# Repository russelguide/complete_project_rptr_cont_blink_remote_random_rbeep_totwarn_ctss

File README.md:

Radio Talking Repeater Controller This is a basic repeater controller. It has a Time speaking clock, blinking led, dfmf remonte control decoder, random rogerbeep function, time out timer for potection and ctcss dedoder, squelch tail timer and Ider timer. The timer lengths can all be changed in the source code. There is an Ider which runs at the end of the Id timer. The Ider message is sent in CW and the message can be change using the Letter codes listed at the end of the source code. There’s an audio control circuit suggestion, which you may find useful. Additionally there should be some type of debounce added to the COS input of the Arduino. Perhaps a cap and resistor to smooth out the CAS transition. This interface will depend on the radio circuit being used.

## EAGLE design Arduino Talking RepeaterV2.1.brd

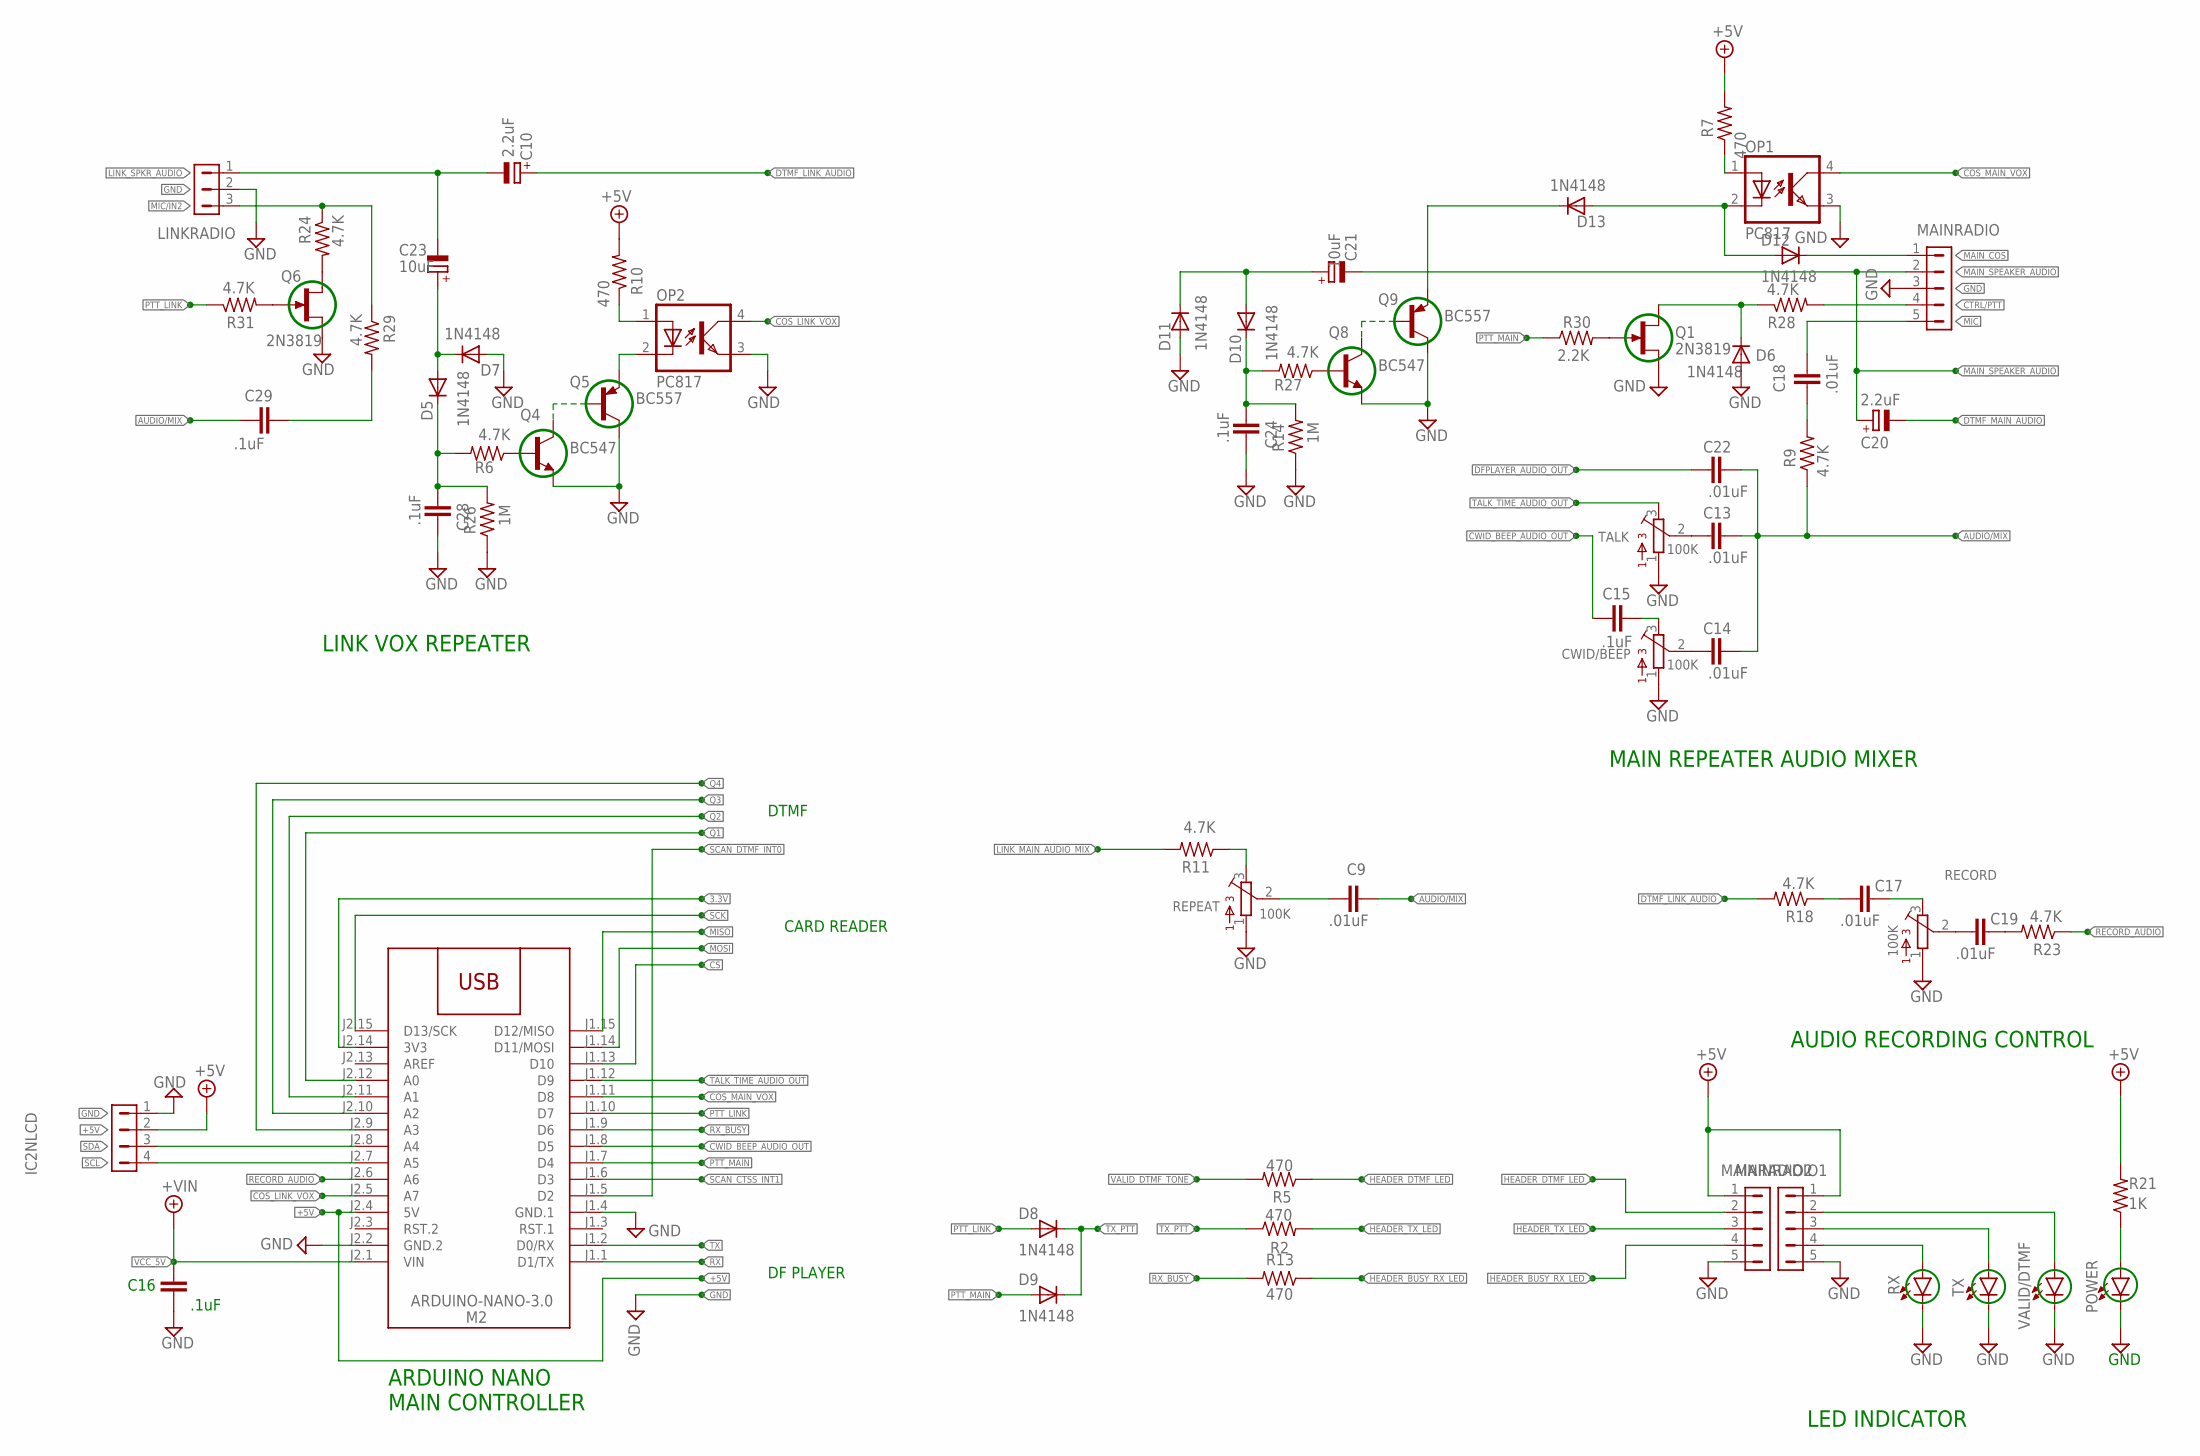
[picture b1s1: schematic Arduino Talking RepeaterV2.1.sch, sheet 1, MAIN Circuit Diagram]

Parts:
C9, C13, C14, C17, C18, C19, C22: .01uF; C5B3
C10, C20: 2.2uF; E2,5-6
C15, C16, C24, C28, C29: .1uF; C5B3
C21, C23: 10uF; E2,5-6
CWID/BEEP: 100K; 3362P
D5, D6, D7, D8, D9, D10, D11, D12, D13: 1N4148; DO35-10
IC2NLCD: HDR-1X4-70543-?; 70543-04
LINKRADIO: HDR-1X3-70543-?; 70543-03
M2: ARDUINO-NANO-3.0
MAINRADIO, MAINRADIO1, MAINRADIO2: HDR-1X5-70543-?; 70543-05
OP1, OP2: PC817; DIL04
POWER: LEDB155; Q62902-B155
Q1, Q6: 2N3819; TO92F
Q4, Q8: BC547; TO92
Q5, Q9: BC557; TO92
R2, R5, R7, R10, R13: 470; 0207/10
R6, R9, R11, R18, R23, R24, R27, R28, R29, R31: 4.7K; 0207/10
R14, R26: 1M; 0207/10
R21: 1K; 0207/10
R30: 2.2K; 0207/10
RECORD: 100K; 3362P
REPEAT: 100K; 3362P
RX: LEDB155; Q62902-B155
TALK: 100K; 3362P
TX: LEDB155; Q62902-B155
VALID/DTMF: LEDB155; Q62902-B155

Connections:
3.3V: M2.J2.14 (3V3); also elsewhere on the board
+5V: IC2NLCD.2, M2.J2.4 (5V), R7.2, R10.2; also elsewhere on the board
AUDIO/MIX: C9.1, C13.1, C14.1, C22.1, C29.1, R9.1
BUSY_RX_LED: MAINRADIO2.4, RX.A (ANODE)
COR: D12.A, D13.A, OP1.2 (C)
COR1: OP2.2 (C), Q5.1 (E)
COS_LINK_VOX: M2.J2.5 (A7), OP2.4 (COL)
COS_MAIN_VOX: M2.J1.11 (D8), OP1.4 (COL)
CS: M2.J1.13 (D10); also elsewhere on the board
CTRL/PTT: MAINRADIO.4, R28.2
CWID_BEEP_AUDIO_OUT: C15.1, M2.J1.8 (D5)
DFPLAYER_AUDIO_OUT: C22.2; also elsewhere on the board
DTMF_LED: MAINRADIO2.2, VALID/DTMF.A (ANODE)
DTMF_LINK_AUDIO: C10.+, R18.2; also elsewhere on the board
DTMF_MAIN_AUDIO: C20.-; also elsewhere on the board
GND: C16.2, C24.1, C28.1, CWID/BEEP.1, D6.A, D7.A, D11.A, IC2NLCD.1, LINKRADIO.2, M2.J1.4 (GND.1), M2.J2.2 (GND.2), MAINRADIO.3, MAINRADIO1.5, MAINRADIO2.5, OP1.3 (EMIT), OP2.3 (EMIT), POWER.K (CATHODE), Q1.S, Q4.1 (E), Q5.3 (C), Q6.S, Q8.1 (E), Q9.3 (C), R14.1, R26.1, RECORD.1, REPEAT.1, RX.K (CATHODE), TALK.1, TX.K (CATHODE), VALID/DTMF.K (CATHODE); also elsewhere on the board
HEADER_BUSY_RX_LED: MAINRADIO1.4, R13.1
HEADER_DTMF_LED: MAINRADIO1.2, R5.1
HEADER_TX_LED: MAINRADIO1.3, R2.2
LINK_MAIN_AUDIO_MIX: R11.2; also elsewhere on the board
LINK_SPKR_AUDIO: C10.-, C23.-, LINKRADIO.1
MAIN_COS: D12.C, MAINRADIO.1
MAIN_SPEAKER_AUDIO: C20.+, C21.-, MAINRADIO.2
MIC: C18.1, MAINRADIO.5
MIC/IN2: LINKRADIO.3, R24.1, R29.1
MISO: M2.J1.15 (D12/MISO); also elsewhere on the board
MOSI: M2.J1.14 (D11/MOSI); also elsewhere on the board
unnamed: OP2.1 (A), R10.1
unnamed: Q4.2 (B), R6.1
unnamed: C15.2, CWID/BEEP.3
unnamed: C18.2, R9.2
unnamed: C29.2, R29.2
unnamed: OP1.1 (A), R7.1
unnamed: C14.2, CWID/BEEP.2
unnamed: R11.1, REPEAT.3
unnamed: C9.2, REPEAT.2
unnamed: C19.2, RECORD.2
unnamed: C17.1, RECORD.3
unnamed: C19.1, R23.2
unnamed: POWER.A (ANODE), R21.1
unnamed: Q8.3 (C), Q9.2 (B)
unnamed: C13.2, TALK.2
unnamed: C21.+, D10.A, D11.C
unnamed: C24.2, D10.C, R14.2, R27.2
unnamed: Q8.2 (B), R27.1
unnamed: C17.2, R18.1
unnamed: D13.C, Q9.1 (E)
unnamed: Q4.3 (C), Q5.2 (B)
unnamed: Q6.D, R24.2
unnamed: Q1.G, R30.2
unnamed: C23.+, D5.A, D7.C
unnamed: C28.2, D5.C, R6.2, R26.2
NA: D6.C, Q1.D, R28.1
PTT: Q6.G, R31.2
PTT_LINK: D8.A, M2.J1.10 (D7), R31.1
PTT_MAIN: D9.A, M2.J1.7 (D4), R30.1
Q1: M2.J2.12 (A0); also elsewhere on the board
Q2: M2.J2.11 (A1); also elsewhere on the board
Q3: M2.J2.10 (A2); also elsewhere on the board
Q4: M2.J2.9 (A3); also elsewhere on the board
RECORD_AUDIO: M2.J2.6 (A6), R23.1
RX: M2.J1.1 (D1/TX); also elsewhere on the board
RX_BUSY: M2.J1.9 (D6), R13.2
SCAN_CTSS_INT1: M2.J1.6 (D3); also elsewhere on the board
SCAN_DTMF_INT0: M2.J1.5 (D2); also elsewhere on the board
SCK: M2.J2.15 (D13/SCK); also elsewhere on the board
SCL: IC2NLCD.4, M2.J2.7 (A5); also elsewhere on the board
SDA: IC2NLCD.3, M2.J2.8 (A4); also elsewhere on the board
TALK_TIME_AUDIO_OUT: M2.J1.12 (D9), TALK.3
TX: M2.J1.2 (D0/RX); also elsewhere on the board
TX_LED: MAINRADIO2.3, TX.A (ANODE)
TX_PTT: D8.C, D9.C, R2.1
VALID_DTMF_TONE: R5.2; also elsewhere on the board
VCC_5V: C16.1, M2.J2.1 (VIN), MAINRADIO1.1, MAINRADIO2.1, R21.2; also elsewhere on the board

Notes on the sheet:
ARDUINO NANO MAIN CONTROLLER
DTMF
CARD READER
MAIN REPEATER AUDIO MIXER
LINK VOX REPEATER
AUDIO RECORDING CONTROL
DF PLAYER
LED INDICATOR

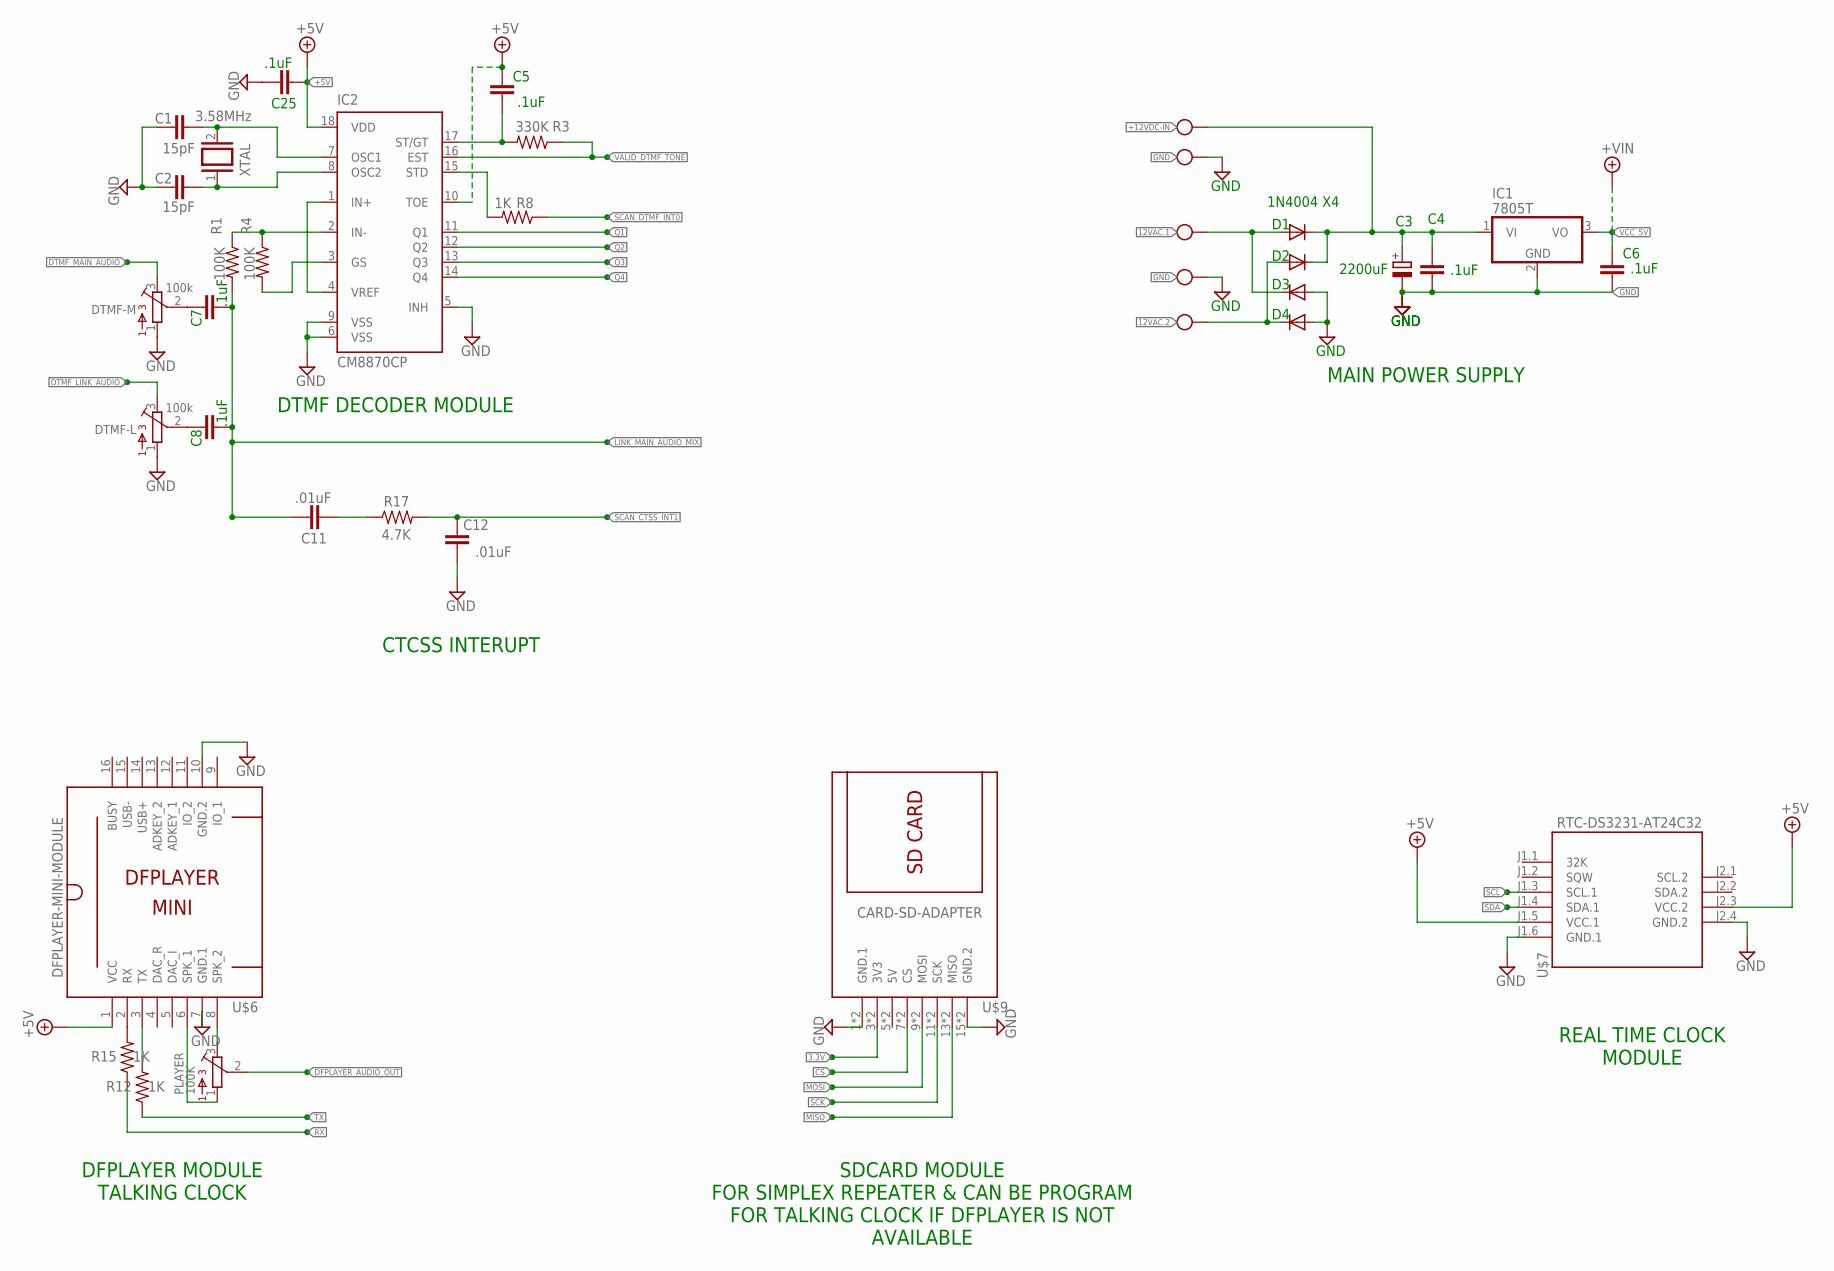
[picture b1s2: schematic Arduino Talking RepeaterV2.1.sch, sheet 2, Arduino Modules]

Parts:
12VDC: AK300/2
AC: AK500/3
C1, C2: 15pF; C050-025X075
C3: 2200uF; E5-13
C4, C5, C6, C7, C8, C25: .1uF; C5B3
C11, C12: .01uF; C5B3
D1, D2, D3: 1N4004; DO41-10
D4: 1N4004 X4; DO41-10
DTMF-L: 100k; 3362P
DTMF-M: 100k; 3362P
IC1: 7805T; TO220H
IC2: CM8870CP; DIL18
PLAYER: 100K; 3362P
R1, R4: 100K; 0207/10
R3: 330K; 0207/10
R8, R12, R15: 1K; 0207/10
R17: 4.7K; 0207/10
U$6: DFPLAYER-MINI-MODULE
U$7: RTC-DS3231-AT24C32
U$9: CARD-SD-ADAPTER
XTAL: 3.58MHz; QS

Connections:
3.3V: U$9.3 (3V3), U$9.4 (3V3); also elsewhere on the board
5V: U$9.5 (5V), U$9.6 (5V)
12VAC.1: AC.1, D1.A, D3.C
12VAC.2: AC.2, D2.A, D4.C
+5V: C5.1, C25.2, IC2.10 (TOE), IC2.18 (VDD), U$6.1 (VCC), U$7.J1.5 (VCC.1), U$7.J2.3 (VCC.2); also elsewhere on the board
+12VDC-IN: 12VDC.2, C3.+, C4.1, D1.C, D2.C, IC1.1 (VI)
CLK: C2.2, IC2.8 (OSC2), XTAL.1
CS: U$9.7 (CS), U$9.8 (CS); also elsewhere on the board
DFPLAYER_AUDIO_OUT: PLAYER.2; also elsewhere on the board
DTMF_LINK_AUDIO: DTMF-L.3; also elsewhere on the board
DTMF_MAIN_AUDIO: DTMF-M.3; also elsewhere on the board
GND: 12VDC.1, AC.3, C1.1, C2.1, C3.-, C4.2, C6.2, C12.2, C25.1, D3.A, D4.A, DTMF-L.1, DTMF-M.1, IC1.2 (GND), IC2.5 (INH), IC2.6 (VSS), IC2.9 (VSS), U$6.7 (GND.1), U$6.10 (GND.2), U$7.J1.6 (GND.1), U$7.J2.4 (GND.2), U$9.1 (GND.1), U$9.2 (GND.1), U$9.15 (GND.2), U$9.16 (GND.2); also elsewhere on the board
LINK_MAIN_AUDIO_MIX: C7.2, C8.2, C11.1, R1.2; also elsewhere on the board
MISO: U$9.13 (MISO), U$9.14 (MISO); also elsewhere on the board
MOSI: U$9.9 (MOSI), U$9.10 (MOSI); also elsewhere on the board
unnamed: IC2.2 (IN-), R1.1, R4.1
unnamed: IC2.3 (GS), R4.2
unnamed: IC2.1 (IN+), IC2.4 (VREF)
unnamed: C1.2, IC2.7 (OSC1), XTAL.2
unnamed: C5.2, IC2.17 (ST/GT), R3.2
unnamed: IC2.15 (STD), R8.2
unnamed: C7.1, DTMF-M.2
unnamed: C8.1, DTMF-L.2
unnamed: C11.2, R17.1
unnamed: R12.2, U$6.3 (TX)
unnamed: R15.2, U$6.2 (RX)
unnamed: PLAYER.3, U$6.8 (SPK_2)
unnamed: PLAYER.1, U$6.6 (SPK_1)
Q1: IC2.11 (Q1); also elsewhere on the board
Q2: IC2.12 (Q2); also elsewhere on the board
Q3: IC2.13 (Q3); also elsewhere on the board
Q4: IC2.14 (Q4); also elsewhere on the board
RX: R15.1; also elsewhere on the board
SCAN_CTSS_INT1: C12.1, R17.2; also elsewhere on the board
SCAN_DTMF_INT0: R8.1; also elsewhere on the board
SCK: U$9.11 (SCK), U$9.12 (SCK); also elsewhere on the board
SCL: U$7.J1.3 (SCL.1); also elsewhere on the board
SDA: U$7.J1.4 (SDA.1); also elsewhere on the board
TX: R12.1; also elsewhere on the board
VALID_DTMF_TONE: IC2.16 (EST), R3.1; also elsewhere on the board
VCC_5V: C6.1, IC1.3 (VO); also elsewhere on the board

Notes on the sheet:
DTMF DECODER MODULE
SDCARD MODULE FOR SIMPLEX REPEATER & CAN BE PROGRAM FOR TALKING CLOCK IF DFPLAYER IS NOT AVAILABLE
REAL TIME CLOCK MODULE
CTCSS INTERUPT
DFPLAYER MODULE TALKING CLOCK
MAIN POWER SUPPLY

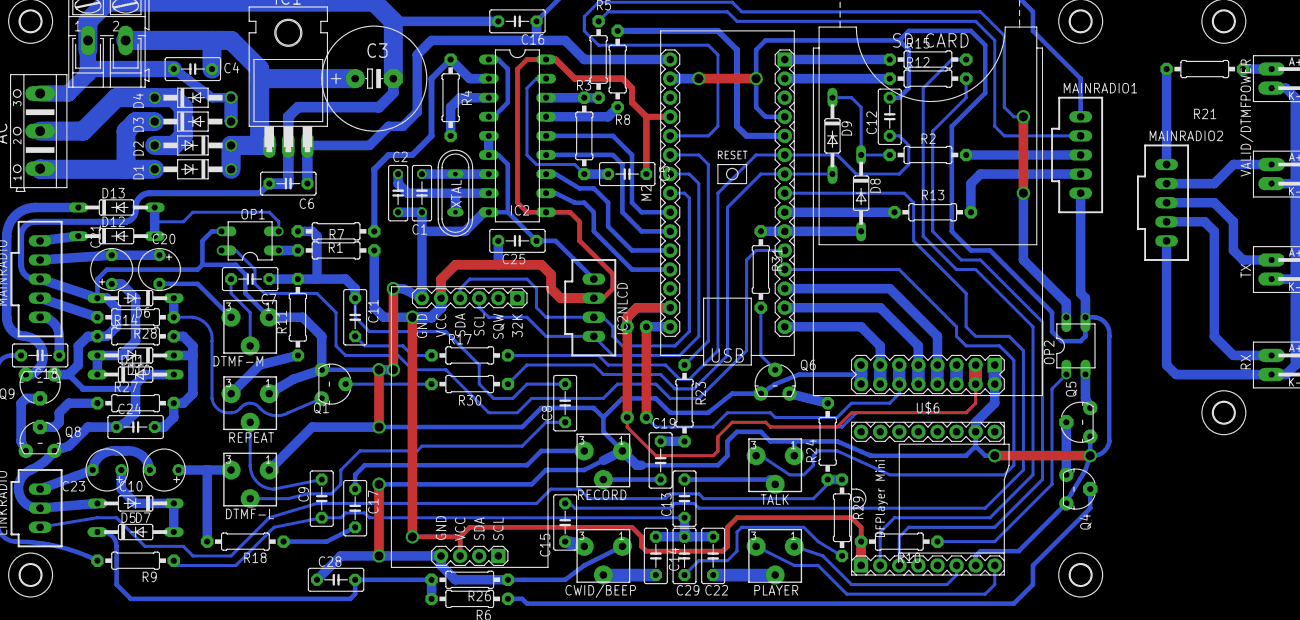
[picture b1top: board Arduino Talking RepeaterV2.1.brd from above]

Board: 2 copper layers, 105 parts (0 on the bottom side), 92 nets.

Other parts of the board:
U$1, U$2, U$3, U$4, U$5, U$8: 2,8

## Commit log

2024-04-22 first and completed
2024-04-22 second commit add eagle cadsoft schematic and board diagram
2024-04-22 Create README.md
    Radio Talking Repeater Controller This is a basic repeater controller. It has a Time speaking clock, blinking led, dfmf remonte control decoder, random rogerbeep function, time out timer for potectio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

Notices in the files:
parts and their libraries:
con-hdrs40: Copyright (C) 2004, Bob Starr (bobstarr@mindspring.com)
diy-modules: Released under the Creative Commons Attribution 4.0 International License: http://creativecommons.org/licenses/by/4.0
